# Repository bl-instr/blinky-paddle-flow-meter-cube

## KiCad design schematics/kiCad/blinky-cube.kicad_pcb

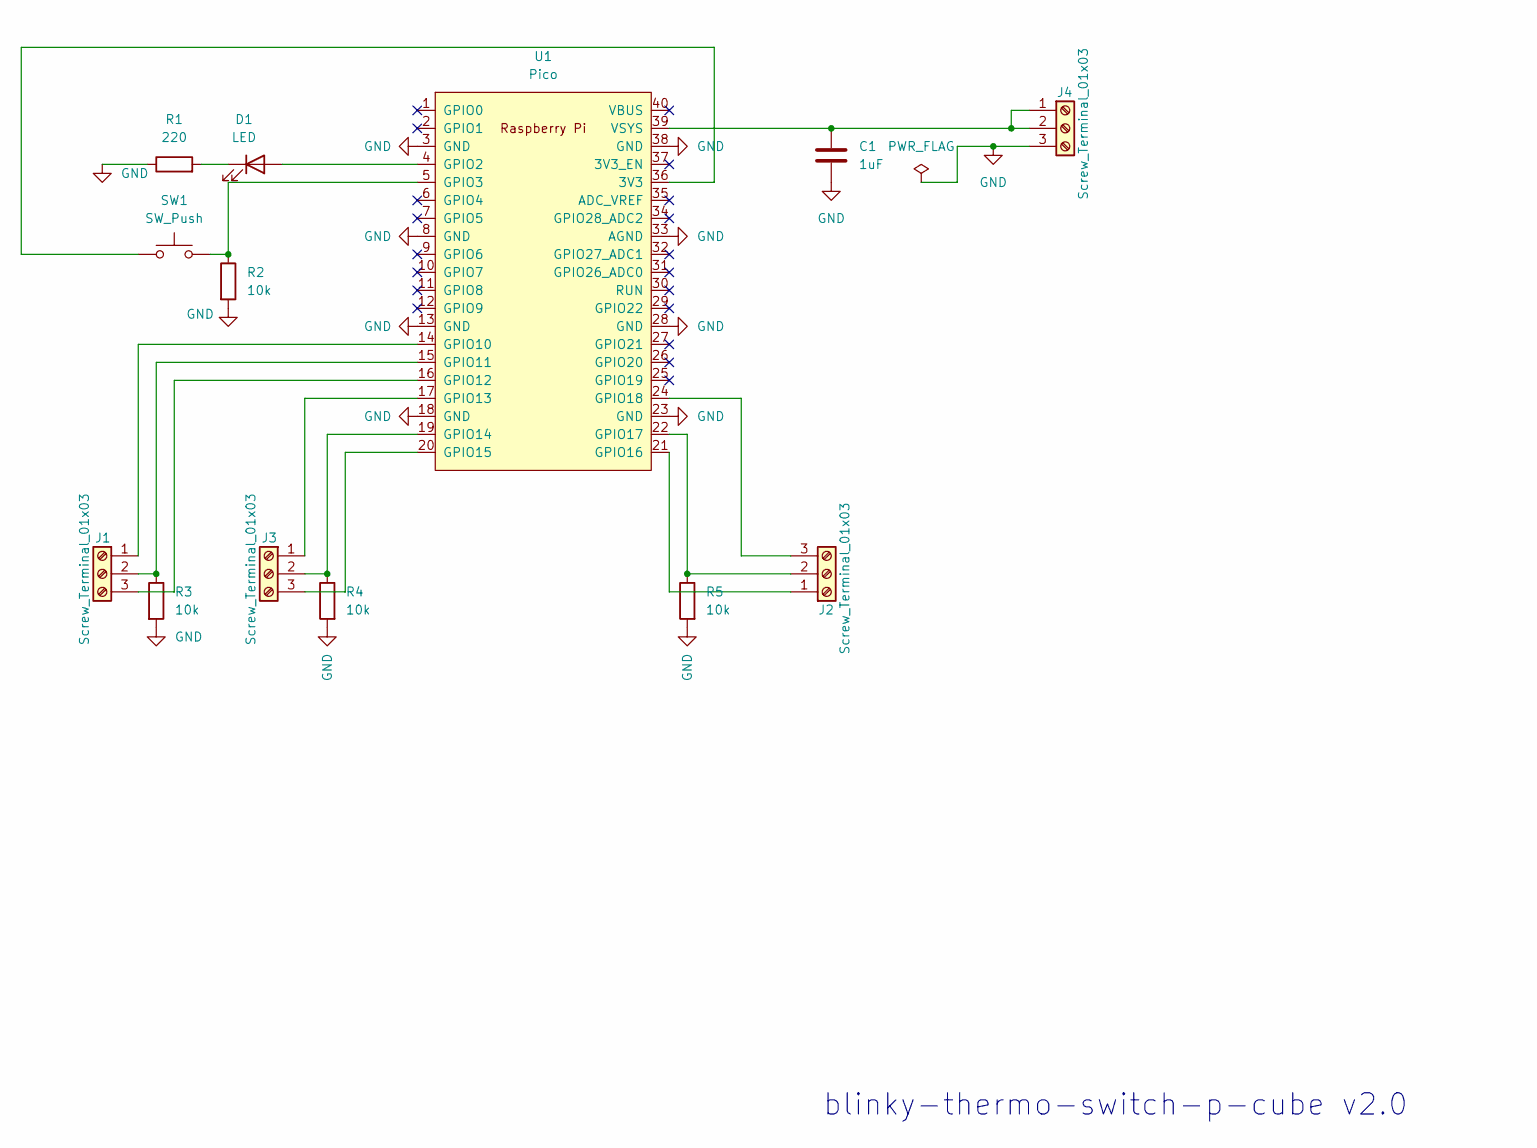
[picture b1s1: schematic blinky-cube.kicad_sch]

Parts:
C1: 1uF; C_1206_3216Metric_Pad1.33x1.80mm_HandSolder
D1: LED; LED_D5.0mm
J1, J2, J3, J4: Screw_Terminal_01x03; TerminalBlock_bornier-3_P5.08mm
R1: 220; R_1206_3216Metric_Pad1.30x1.75mm_HandSolder
R2, R3, R4, R5: 10k; R_1206_3216Metric_Pad1.30x1.75mm_HandSolder
SW1: SW_Push; SW_PUSH_6mm
U1: Pico; RPi_Pico_SMD_TH

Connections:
GND: C1.2, J4.3, R1.1, R2.2, R3.2, R4.2, R5.2, U1.3 (GND), U1.8 (GND), U1.13 (GND), U1.18 (GND), U1.23 (GND), U1.28 (GND), U1.33 (AGND), U1.38 (GND)
unnamed: D1.2 (A), U1.4 (GPIO2)
unnamed: D1.1 (K), R1.2
unnamed: J1.1, U1.14 (GPIO10)
unnamed: J1.2, R3.1, U1.15 (GPIO11)
unnamed: J1.3, U1.16 (GPIO12)
unnamed: J2.1, U1.21 (GPIO16)
unnamed: J2.2, R5.1, U1.22 (GPIO17)
unnamed: J2.3, U1.24 (GPIO18)
unnamed: J3.1, U1.17 (GPIO13)
unnamed: J3.2, R4.1, U1.19 (GPIO14)
unnamed: J3.3, U1.20 (GPIO15)
unnamed: C1.1, J4.1, J4.2, U1.39 (VSYS)
unnamed: SW1.1, U1.36 (3V3)
unnamed: R2.1, SW1.2, U1.5 (GPIO3)

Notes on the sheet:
blinky-thermo-switch-p-cube v2.0

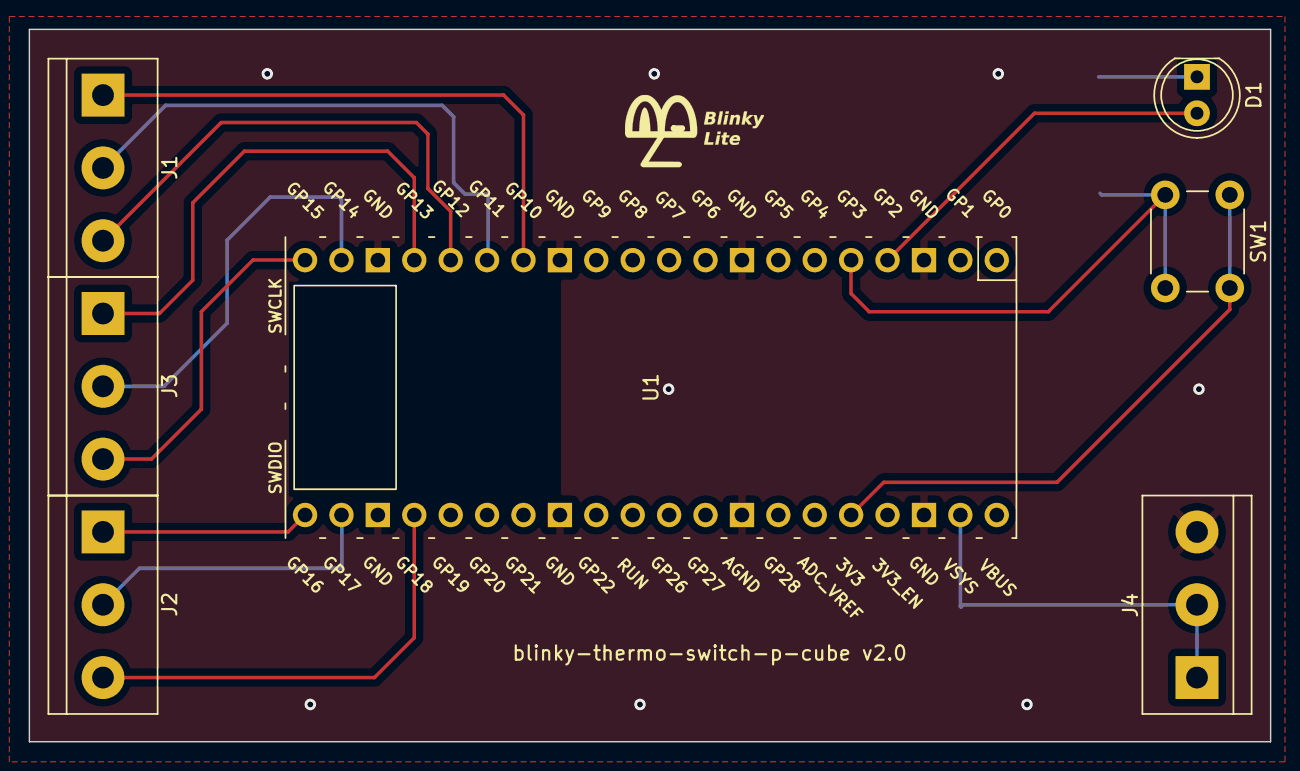
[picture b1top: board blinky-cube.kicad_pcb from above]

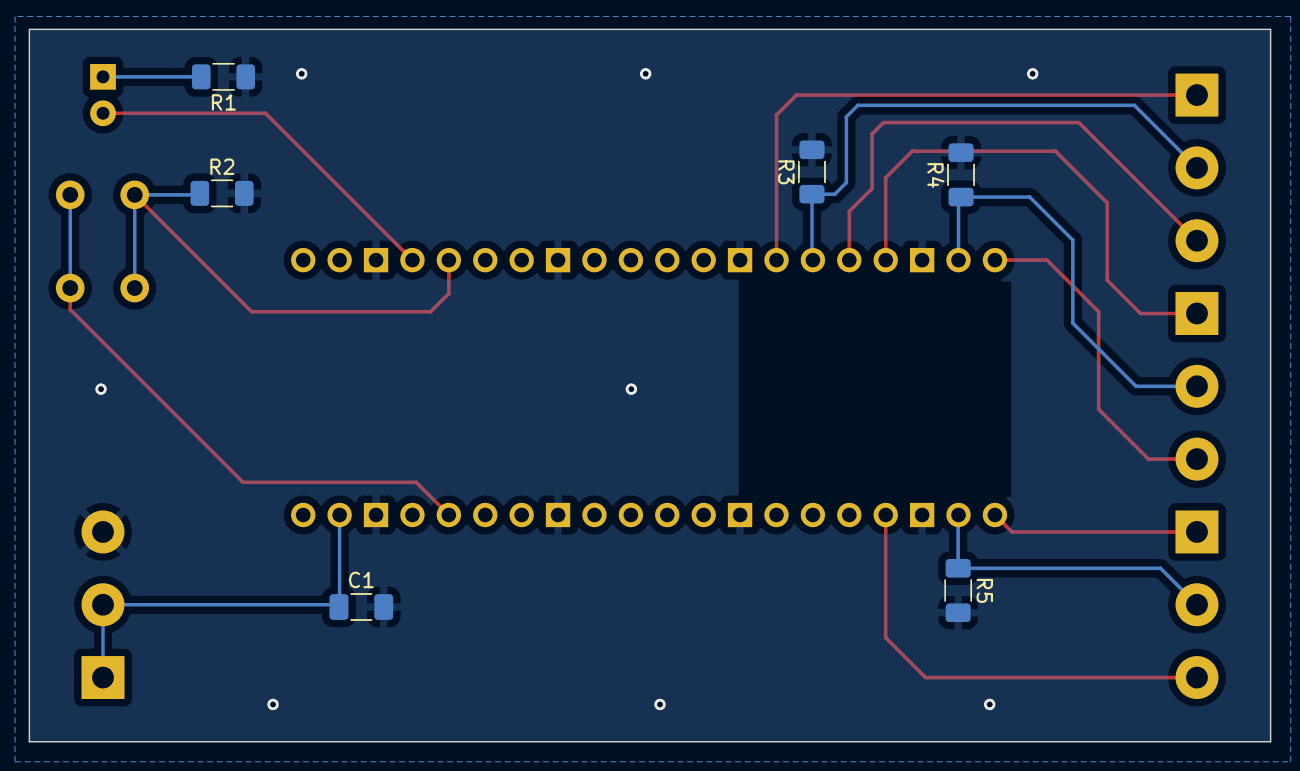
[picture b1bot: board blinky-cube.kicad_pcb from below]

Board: 2 copper layers, 86.6 x 49.7 mm, 13 parts (6 on the bottom side), 15 nets.

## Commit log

2024-02-21 settings readings working
2024-02-22 added bom
2024-03-03 added wifi reboot after too may attempts
2024-03-16 having issues connecting sometimes
2024-03-20 print diagnostics false
2024-03-20 added one-core
2024-10-22 added flow meter code
2024-11-04 changed name to blinky-interlock
2025-02-14 working with picoW
2026-06-06 handled no flow properly
